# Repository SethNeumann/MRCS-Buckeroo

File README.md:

MRCS-Buckeroo

## License: Creative Commons Attribution-NonCommercial-ShareAlike

MRCS-Buckeroo

Model Railroad projects often require one or more power supplies for lighting and electronics powered from an 
auxilliary powr bus, usually 12VDC or a local "wall wart" power supply.  Commercial bucking supplies based on
LM 2596 or boosters based on XL6009 offere an inexpensive basis for developing any voltage from 3-35 volts with 
an input of 3-25 volts by choosing and adjusting an appropriate module.  

The Buckeroo has a 2.1 x 5.5 mm barrel connector and a 3.5mm screw terminal for input and 12 x 0.100 terminals 
power and ground out.  You may also use it as a power distribution block for layout bus power or a wall wart 
without further conversion by omitting the converter and jumpering around its pads.

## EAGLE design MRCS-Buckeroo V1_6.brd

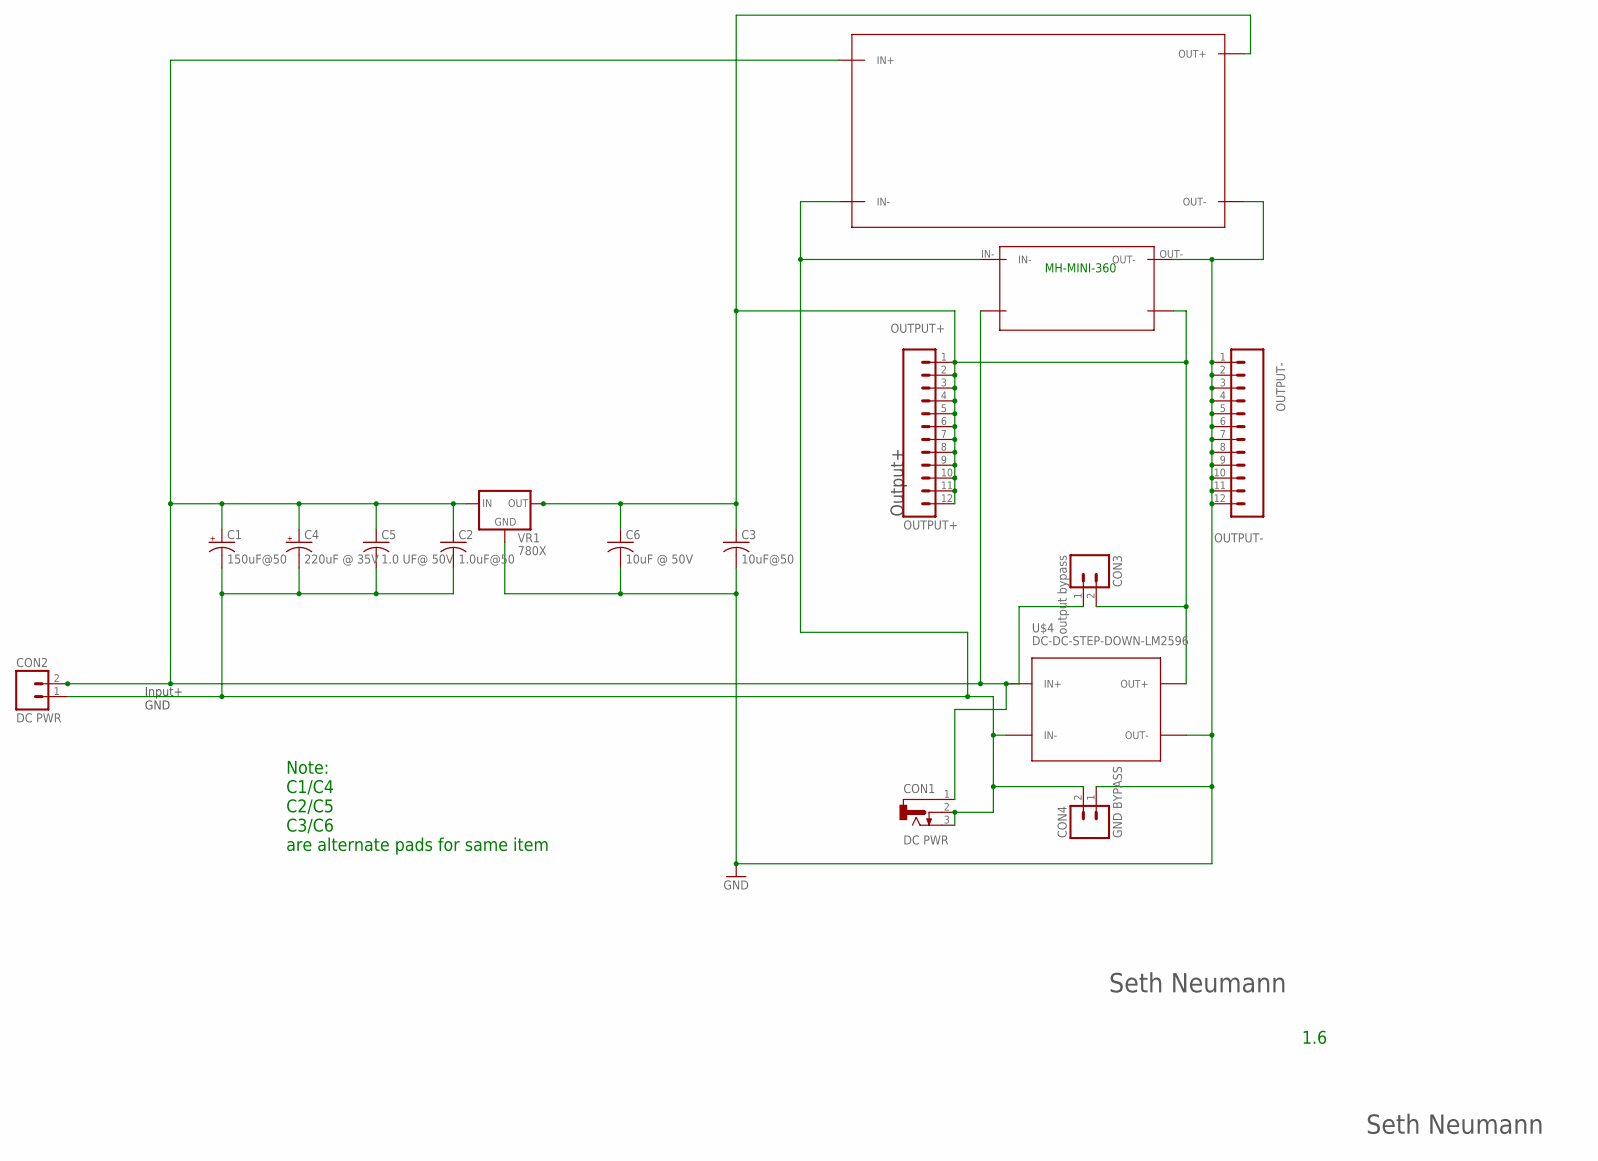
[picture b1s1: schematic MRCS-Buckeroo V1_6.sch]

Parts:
C1: 150uF@50; E5-10.5
C2: 1.0uF@50; C-PTH-0.100
C3: 10uF@50; C-PTH-0.100
C4: 220uF @ 35V; E2.5-6
C5: 1.0 UF@ 50V; C050-024X044
C6: 10uF @ 50V; C050-024X044
CON1: DC PWR; DCJ0202
CON2: DC PWR; SCREWTERMINAL-3.5MM-2_LOCK
CON3: output bypass; MOLEX-1X2_LOCK
CON4: GND BYPASS; MOLEX-1X2_LOCK
MH-MINI-360: MH-MINI-360
OUTPUT+: OUTPUT+; 1X12_LOCK
OUTPUT-: OUTPUT-; 1X12_LOCK
U$4: DC-DC-STEP-DOWN-LM2596
U$5: XL6009BOARD; XL6009_BOARD
VR1: 780X; TO-220-RA

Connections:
GND: C1.-, C2.2, C3.2, C4.-, C5.2, C6.2, CON1.2, CON1.3, CON2.1 (A), CON4.1 (A), CON4.2 (B), MH-MINI-360.IN-, MH-MINI-360.OUT-, OUTPUT-.1, OUTPUT-.2, OUTPUT-.3, OUTPUT-.4, OUTPUT-.5, OUTPUT-.6, OUTPUT-.7, OUTPUT-.8, OUTPUT-.9, OUTPUT-.10, OUTPUT-.11, OUTPUT-.12, U$4.IN-, U$4.OUT-, U$5.IN-, U$5.OUT-, VR1.GND
INPUT+: C1.+, C2.1, C4.+, C5.1, CON1.1, CON2.2 (B), CON3.1 (A), MH-MINI-360.INN+, U$4.IN+, U$5.IN+, VR1.IN
OUTPUT+: C3.1, C6.1, CON3.2 (B), MH-MINI-360.OUTT+, OUTPUT+.1, OUTPUT+.2, OUTPUT+.3, OUTPUT+.4, OUTPUT+.5, OUTPUT+.6, OUTPUT+.7, OUTPUT+.8, OUTPUT+.9, OUTPUT+.10, OUTPUT+.11, OUTPUT+.12, U$4.OUT+, U$5.OUT+, VR1.OUT

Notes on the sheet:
Output+
Input+ GND
Seth Neumann
MH-MINI-360
1.6
Note: C1/C4 C2/C5 C3/C6 are alternate pads for same item

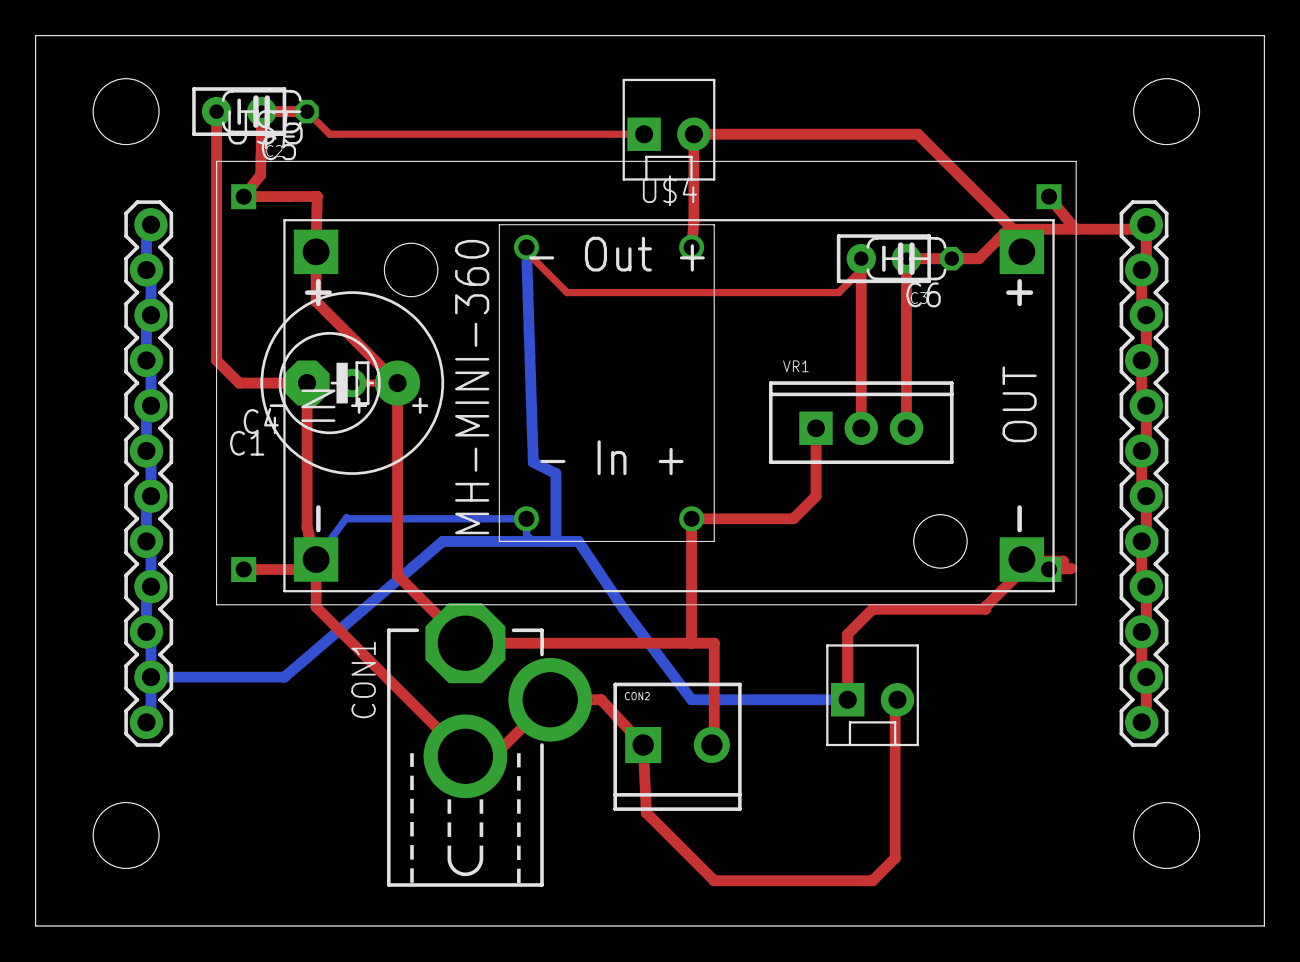
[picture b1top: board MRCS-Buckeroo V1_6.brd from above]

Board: 2 copper layers, 69.0 x 50.0 mm, 19 parts (0 on the bottom side), 3 nets.

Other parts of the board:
U$1: CA-PROP65WARNING
U$2: MRCSLOGOTOP
U$3: MRCSLOGOBTM

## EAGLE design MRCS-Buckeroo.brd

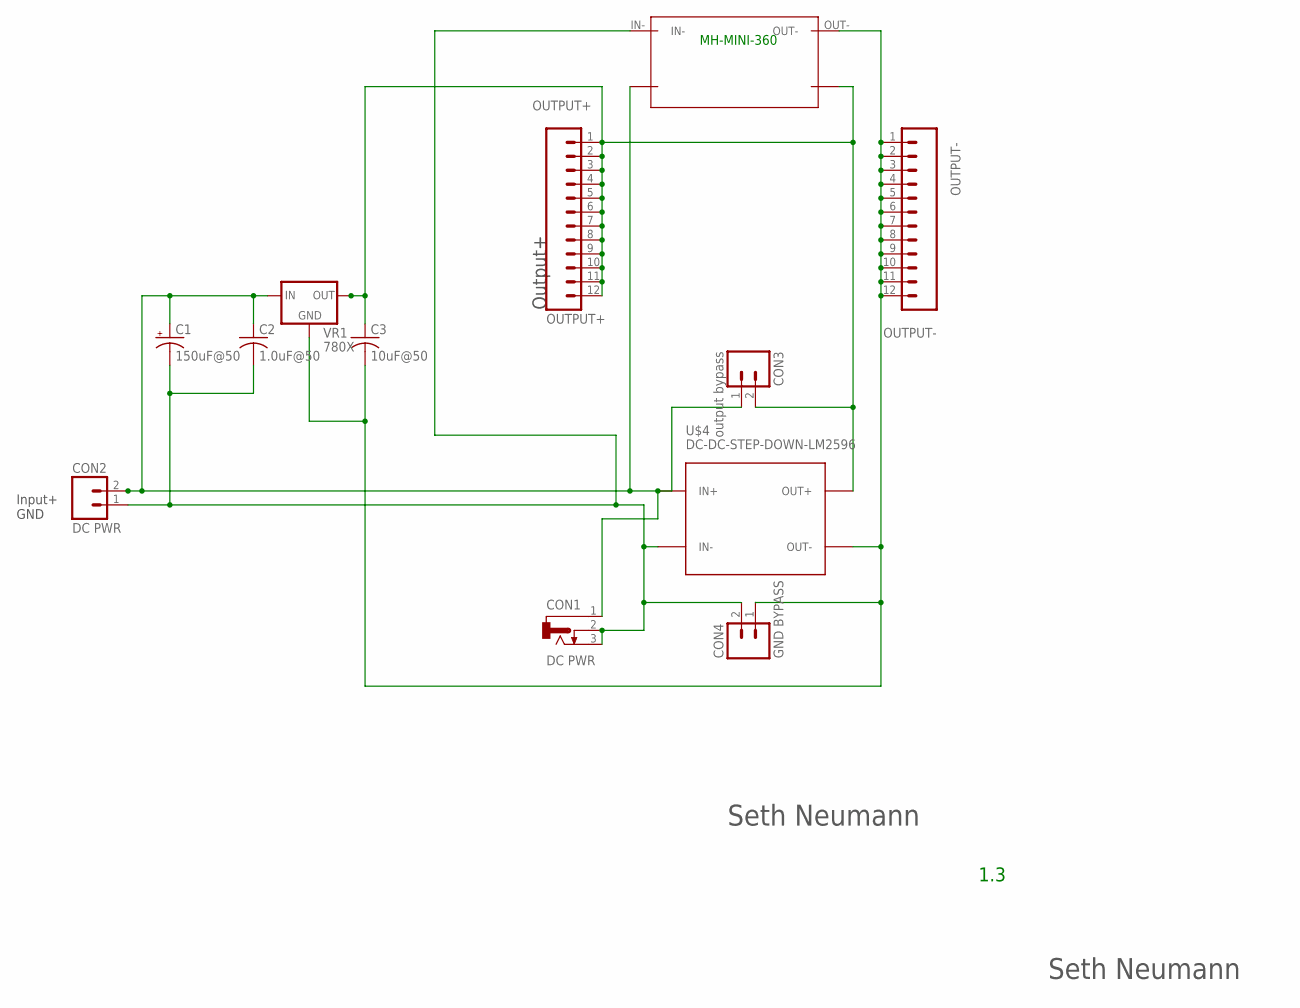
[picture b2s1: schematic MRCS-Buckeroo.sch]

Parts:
C1: 150uF@50; E5-10.5
C2: 1.0uF@50; C-PTH-0.100
C3: 10uF@50; C-PTH-0.100
CON1: DC PWR; DCJ0202
CON2: DC PWR; SCREWTERMINAL-3.5MM-2_LOCK
CON3: output bypass; MOLEX-1X2_LOCK
CON4: GND BYPASS; MOLEX-1X2_LOCK
MH-MINI-360: MH-MINI-360
OUTPUT+: OUTPUT+; 1X12_LOCK
OUTPUT-: OUTPUT-; 1X12_LOCK
U$4: DC-DC-STEP-DOWN-LM2596
VR1: 780X; TO-220-RA

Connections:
GND: C1.-, C2.2, CON1.2, CON1.3, CON2.1 (A), CON4.2 (B), MH-MINI-360.IN-, U$4.IN-; also elsewhere on the board
INPUT+: C1.+, C2.1, CON1.1, CON2.2 (B), CON3.1 (A), MH-MINI-360.INN+, U$4.IN+, VR1.IN; also elsewhere on the board
OUTPUT+: C3.1, CON3.2 (B), MH-MINI-360.OUTT+, OUTPUT+.1, OUTPUT+.2, OUTPUT+.3, OUTPUT+.4, OUTPUT+.5, OUTPUT+.6, OUTPUT+.7, OUTPUT+.8, OUTPUT+.9, OUTPUT+.10, OUTPUT+.11, OUTPUT+.12, U$4.OUT+, VR1.OUT; also elsewhere on the board
OUTPUT-: C3.2, CON4.1 (A), MH-MINI-360.OUT-, OUTPUT-.1, OUTPUT-.2, OUTPUT-.3, OUTPUT-.4, OUTPUT-.5, OUTPUT-.6, OUTPUT-.7, OUTPUT-.8, OUTPUT-.9, OUTPUT-.10, OUTPUT-.11, OUTPUT-.12, U$4.OUT-, VR1.GND; also elsewhere on the board

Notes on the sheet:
Output+
Input+ GND
Seth Neumann
MH-MINI-360
1.3

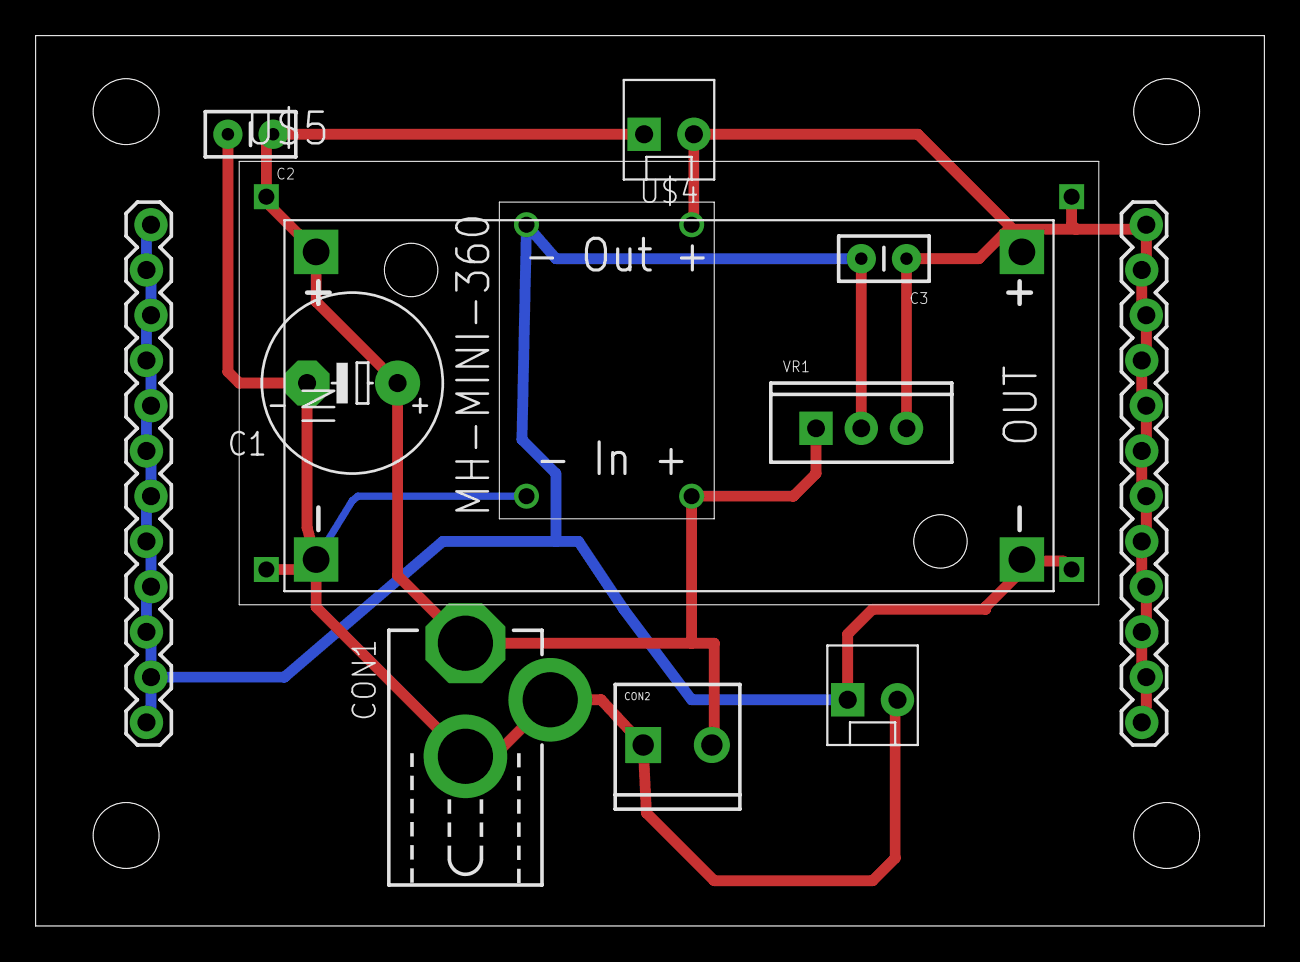
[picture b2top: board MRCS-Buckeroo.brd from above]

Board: 2 copper layers, 69.0 x 50.0 mm, 16 parts (0 on the bottom side), 4 nets.

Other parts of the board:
U$1: CA-PROP65WARNING
U$2: MRCSLOGOTOP
U$3: MRCSLOGOBTM
U$5: XL6009BOARD; XL6009_BOARD

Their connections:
GND: U$5.IN-; also elsewhere on the board
INPUT+: U$5.IN+; also elsewhere on the board
OUTPUT+: U$5.OUT+; also elsewhere on the board
OUTPUT-: U$5.OUT-; also elsewhere on the board

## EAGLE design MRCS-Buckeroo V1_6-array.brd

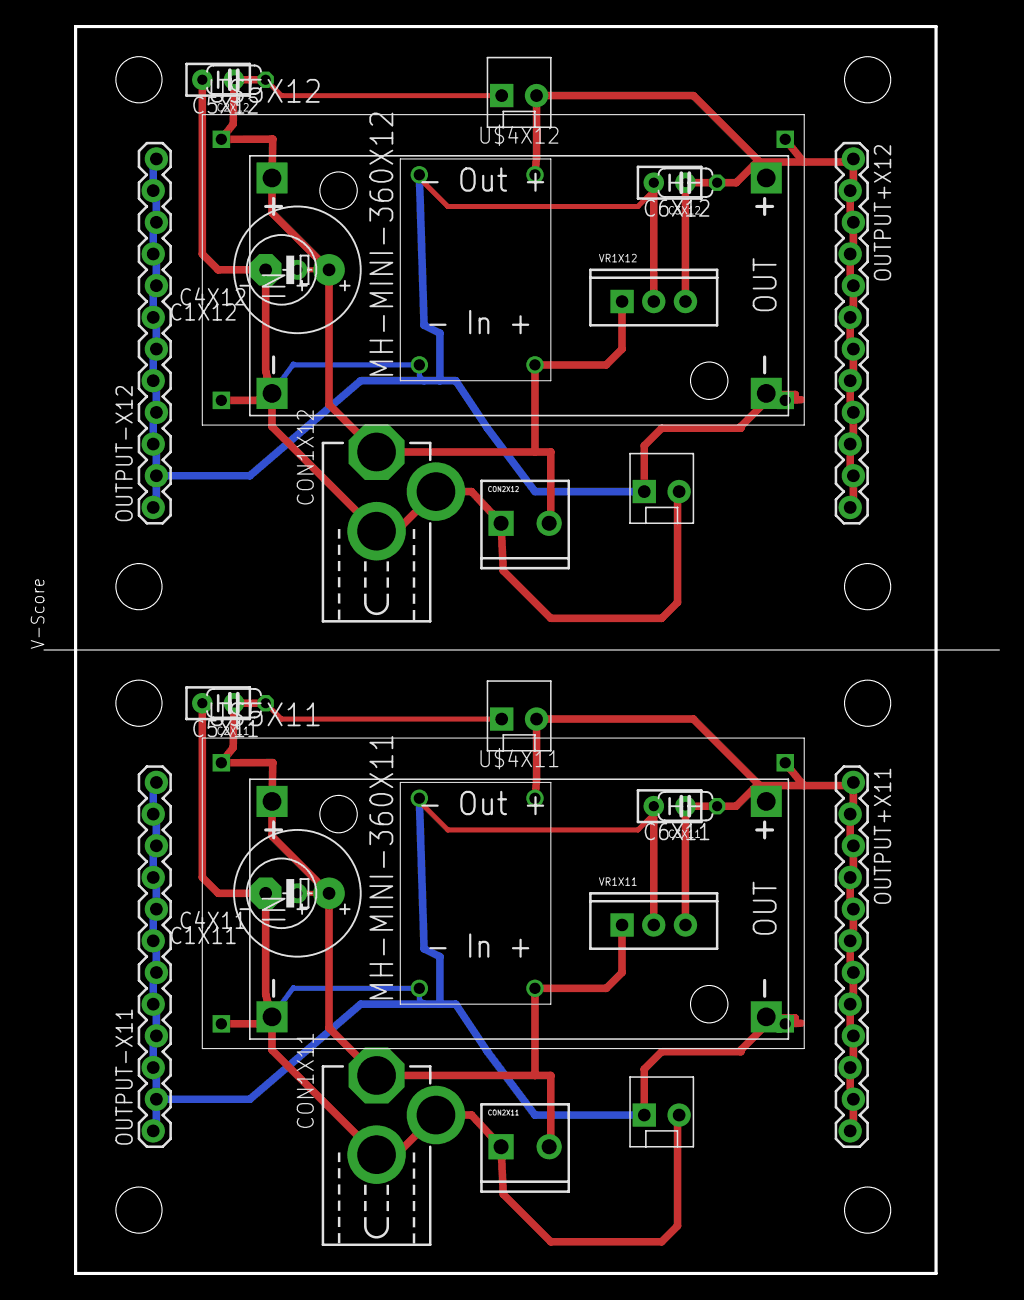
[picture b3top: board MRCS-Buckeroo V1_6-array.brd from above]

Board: 2 copper layers, 77.9 x 100.0 mm, 38 parts (0 on the bottom side), 6 nets.

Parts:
C1X11, C1X12: 150uF@50; E5-10.5
C2X11, C2X12: 1.0uF@50; C-PTH-0.100
C3X11, C3X12: 10uF@50; C-PTH-0.100
C4X11, C4X12: 220uF @ 35V; E2.5-6
C5X11, C5X12: 1.0 UF@ 50V; C050-024X044
C6X11, C6X12: 10uF @ 50V; C050-024X044
CON1X11, CON1X12: DC PWR; DCJ0202
CON2X11, CON2X12: DC PWR; SCREWTERMINAL-3.5MM-2_LOCK
CON3X11, CON3X12: output bypass; MOLEX-1X2_LOCK
CON4X11, CON4X12: GND BYPASS; MOLEX-1X2_LOCK
MH-MINI-360X11, MH-MINI-360X12: MH-MINI-360
OUTPUT+X11, OUTPUT+X12: OUTPUT+; 1X12_LOCK
OUTPUT-X11, OUTPUT-X12: OUTPUT-; 1X12_LOCK
U$1X11, U$1X12: CA-PROP65WARNING
U$2X11, U$2X12: MRCSLOGOTOP
U$3X11, U$3X12: MRCSLOGOBTM
U$4X11, U$4X12: DC-DC-STEP-DOWN-LM2596
U$5X11, U$5X12: XL6009BOARD; XL6009_BOARD
VR1X11, VR1X12: 780X; TO-220-RA

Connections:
GNDX11: C1X11.-, C2X11.2, C3X11.2, C4X11.-, C5X11.2, C6X11.2, CON1X11.2, CON1X11.3, CON2X11.1, CON4X11.1, CON4X11.2, MH-MINI-360X11.IN-, MH-MINI-360X11.OUT-, OUTPUT-X11.1, OUTPUT-X11.2, OUTPUT-X11.3, OUTPUT-X11.4, OUTPUT-X11.5, OUTPUT-X11.6, OUTPUT-X11.7, OUTPUT-X11.8, OUTPUT-X11.9, OUTPUT-X11.10, OUTPUT-X11.11, OUTPUT-X11.12, U$4X11.IN-, U$4X11.OUT-, U$5X11.IN-, U$5X11.OUT-, VR1X11.GND
GNDX12: C1X12.-, C2X12.2, C3X12.2, C4X12.-, C5X12.2, C6X12.2, CON1X12.2, CON1X12.3, CON2X12.1, CON4X12.1, CON4X12.2, MH-MINI-360X12.IN-, MH-MINI-360X12.OUT-, OUTPUT-X12.1, OUTPUT-X12.2, OUTPUT-X12.3, OUTPUT-X12.4, OUTPUT-X12.5, OUTPUT-X12.6, OUTPUT-X12.7, OUTPUT-X12.8, OUTPUT-X12.9, OUTPUT-X12.10, OUTPUT-X12.11, OUTPUT-X12.12, U$4X12.IN-, U$4X12.OUT-, U$5X12.IN-, U$5X12.OUT-, VR1X12.GND
INPUT+X11: C1X11.+, C2X11.1, C4X11.+, C5X11.1, CON1X11.1, CON2X11.2, CON3X11.1, MH-MINI-360X11.INN+, U$4X11.IN+, U$5X11.IN+, VR1X11.IN
INPUT+X12: C1X12.+, C2X12.1, C4X12.+, C5X12.1, CON1X12.1, CON2X12.2, CON3X12.1, MH-MINI-360X12.INN+, U$4X12.IN+, U$5X12.IN+, VR1X12.IN
OUTPUT+X11: C3X11.1, C6X11.1, CON3X11.2, MH-MINI-360X11.OUTT+, OUTPUT+X11.1, OUTPUT+X11.2, OUTPUT+X11.3, OUTPUT+X11.4, OUTPUT+X11.5, OUTPUT+X11.6, OUTPUT+X11.7, OUTPUT+X11.8, OUTPUT+X11.9, OUTPUT+X11.10, OUTPUT+X11.11, OUTPUT+X11.12, U$4X11.OUT+, U$5X11.OUT+, VR1X11.OUT
OUTPUT+X12: C3X12.1, C6X12.1, CON3X12.2, MH-MINI-360X12.OUTT+, OUTPUT+X12.1, OUTPUT+X12.2, OUTPUT+X12.3, OUTPUT+X12.4, OUTPUT+X12.5, OUTPUT+X12.6, OUTPUT+X12.7, OUTPUT+X12.8, OUTPUT+X12.9, OUTPUT+X12.10, OUTPUT+X12.11, OUTPUT+X12.12, U$4X12.OUT+, U$5X12.OUT+, VR1X12.OUT

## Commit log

2020-09-29 initial commit
    initial commit
2020-09-29 initial coimmit
    initial commit
2020-09-30 sent to fab
    sent to fab
2020-10-01 clean up working directory
2020-12-08 Added 1st pass of documentation
    Assembly and Installation Instructions
2020-12-08 fixed connector designations
    fixed connector designations, corrected panel to 2
2020-12-08 fix error in scehmatic revision, BOM not displaying
    fix error in scehmatic revision, BOM not displaying
2020-12-20 cleaned out work and derivative files
    cleaned out work and derivative files
2021-01-02 Update INFO
2022-11-14 Added regulator options
    Supports MH-Mini-360 bucking converter and 780X TO-220 linear regulators
2023-01-06 Release 3 sent out for fab
    These include the mini bucker and an updown bucker as well as the pads for 780X TO220 packages. These need to be tested before panelization.
2023-01-30 V1.5 sent out for fab
2023-04-03 Panelized Version1.6
    all works, now panelized 2 up
2023-04-03 V1.6 changes
    panelized

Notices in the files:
parts and their libraries:
diy-modules: Released under the Creative Commons Attribution 4.0 International License: http://creativecommons.org/licenses/by/4.0
